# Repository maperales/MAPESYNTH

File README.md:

# MAPESYNTH
Documentación y ficheros de diseño y programación del sistema Mapesynth
-
En este repositorio se encuentra toda la información necesaria para poder replicar el sistema MAPESYNTH completo.

El sistema MAPESYNTH (Midi Advanced Programmable Educational Synthesizer) es un dispositivo que, convenientemente programado, puede hacer de instrumento MIDI, controlador MIDI, secuenciador MIDI y sintetizador MIDI, o cualquier combinación de las anteriores. Al ser de código abierto, puede ser reprogramado para cumplir otras funciones.

El hardware tiene la estructura de un Boosterpack tipo XL (40 pines), que se puede acomodar sobre multitud de Launchpads de Texas Instruments. En concreto, los ejemplos software y el diseño están enfocados al uso del microcontrolador MSP430FR5994, por lo que será necesario disponer del Launchpad MSP-EXP430FR5994 para su manejo. Los ficheros de diseño se encuentran en Eagle, aunque la etapa final se ha realizado en EasyEDA. Se ofrece igualmente el fichero de EasyEDA, por si sólo se desea fabricar tal cual, sin ningún cambio.

El software se ha desarrollado en Code Composer Studio, disponible de manera gratuita en la página de Texas Instruments. Probablemente se pueda reutilizar con algunos cambios menores con otros compiladores de la familia MSP430, aunque no se ha probado.

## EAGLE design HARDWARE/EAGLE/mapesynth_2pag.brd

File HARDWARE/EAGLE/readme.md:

Ficheros EAGLE
--
En principio, bastará con copiar los ficheros .brd y .sch en el mismo directorio para poder abrirlos. El fichero de librería (.lbr) se ofrece como compilación de los elementos, pero probablemente no sea necesario.

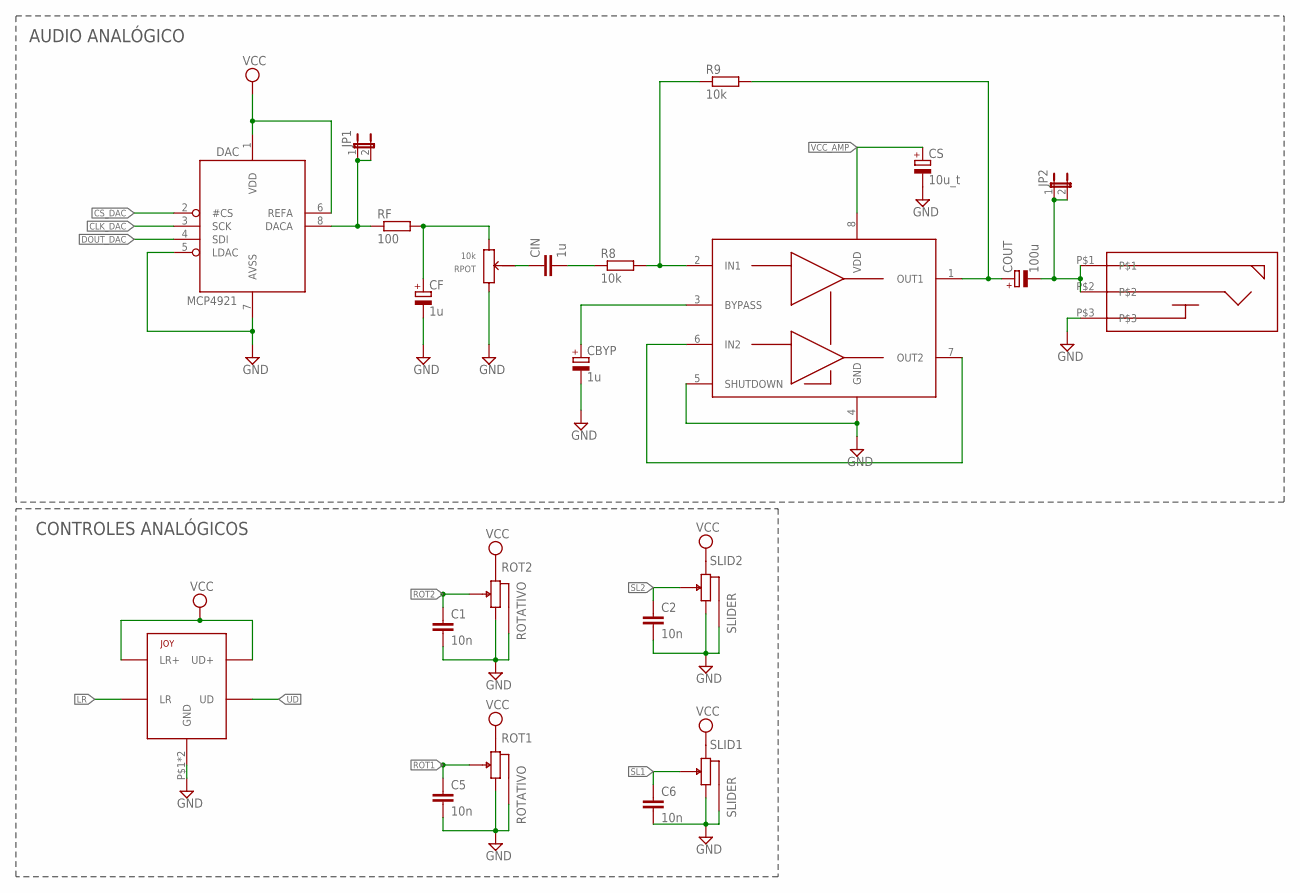
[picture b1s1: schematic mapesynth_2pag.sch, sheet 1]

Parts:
AMP: TPA6111; SO-08
C1, C2, C5, C6: 10n; C050-024X044
CBYP: 1u; 153CLV-0405
CF: 1u; 153CLV-0405
CIN: 1u; C1206
COUT: 100u; 153CLV-0605
CS: 10u_t; CT3528
DAC: MCP4921EN_SMD; SO-08
JOY: JOYSTICK; PLACAJSTICK
JP1, JP2: JP1E; JP1
R8, R9: 10k; M1206
RF: 100; M1206
ROT1, ROT2: ROTATIVO
RPOT: 10k; POT_VOL
SLID1, SLID2: SLIDER
U$4: JACK_3_5MM_VA; JACK3_5MM_V2

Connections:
CLK_DAC: DAC.3 (SCK); also elsewhere on the board
CS_DAC: DAC.2 (#CS); also elsewhere on the board
DOUT_DAC: DAC.4 (SDI); also elsewhere on the board
GND: AMP.4 (GND), AMP.5 (SHUTDOWN), C1.2, C2.2, C5.2, C6.2, CBYP.-, CF.-, CS.-, DAC.5 (LDAC), DAC.7 (AVSS), JOY.P$1 (GND), JOY.P$8 (GND), ROT1.A (1), ROT1.GND1 (GND), ROT1.GND2 (GND), ROT2.A (1), ROT2.GND1 (GND), ROT2.GND2 (GND), RPOT.P$1, SLID1.1, SLID1.4 (GND), SLID1.5 (GND), SLID1.6 (GND), SLID1.7 (GND), SLID2.1, SLID2.4 (GND), SLID2.5 (GND), SLID2.6 (GND), SLID2.7 (GND), U$4.P$3; also elsewhere on the board
LR: JOY.P$3 (LR), JOY.P$6 (LR); also elsewhere on the board
unnamed: DAC.8 (DACA), JP1.1, JP1.2, RF.1
unnamed: CF.+, RF.2, RPOT.P$3
unnamed: CIN.1, RPOT.P$2
unnamed: CIN.2, R8.1
unnamed: AMP.2 (IN1), R8.2, R9.1
unnamed: AMP.1 (OUT1), COUT.+, R9.2
unnamed: COUT.-, JP2.1, JP2.2, U$4.P$1, U$4.P$2
unnamed: AMP.6 (IN2), AMP.7 (OUT2)
unnamed: AMP.3 (BYPASS), CBYP.+
ROT1: C5.1, ROT1.C (2); also elsewhere on the board
ROT2: C1.1, ROT2.C (2); also elsewhere on the board
SL1: C6.1, SLID1.2; also elsewhere on the board
SL2: C2.1, SLID2.2; also elsewhere on the board
UD: JOY.P$2 (UD), JOY.P$7 (UD); also elsewhere on the board
VCC: DAC.1 (VDD), DAC.6 (REFA), JOY.P$4 (LR+), JOY.P$5 (UD+), ROT1.B (3), ROT2.B (3), SLID1.3, SLID2.3; also elsewhere on the board
VCC_AMP: AMP.8 (VDD), CS.+; also elsewhere on the board

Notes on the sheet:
AUDIO ANALÓGICO
CONTROLES ANALÓGICOS

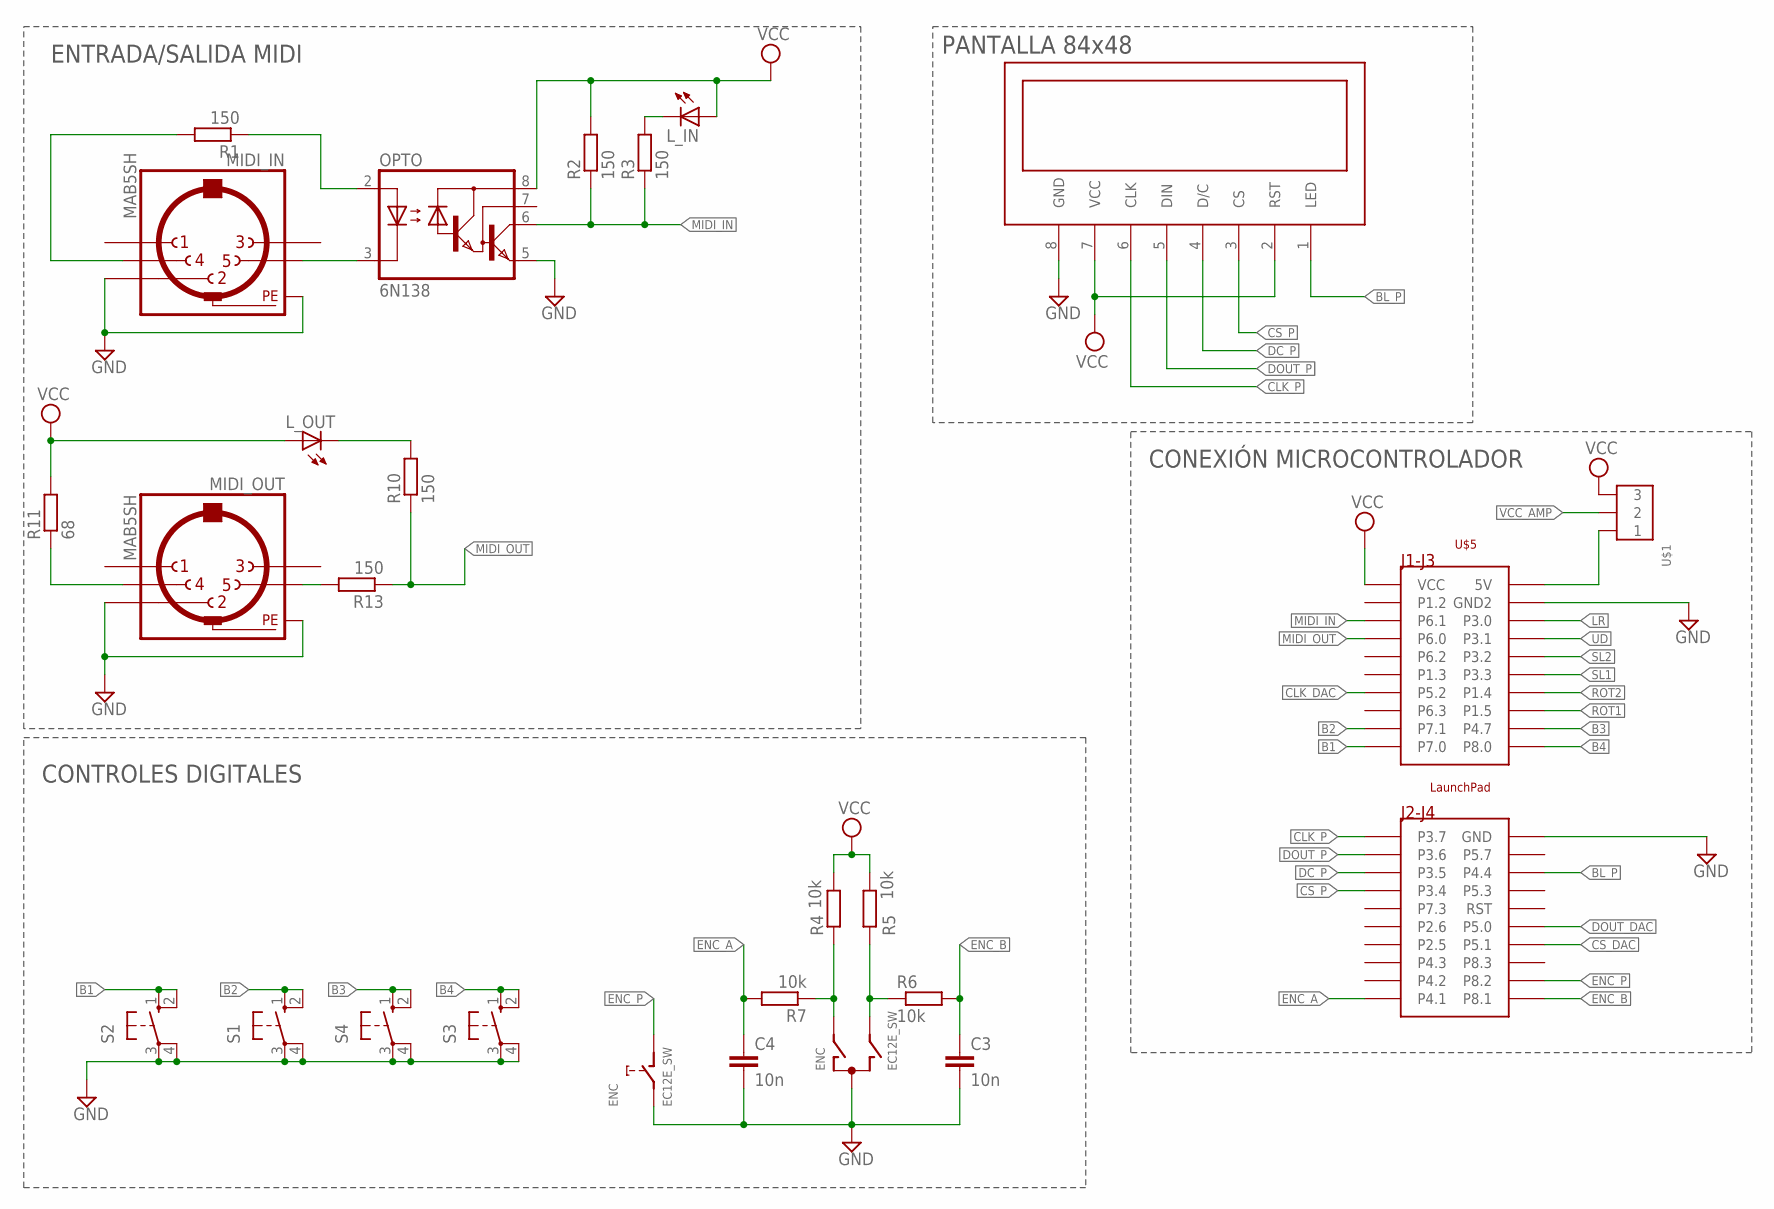
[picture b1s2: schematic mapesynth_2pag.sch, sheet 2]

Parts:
C3, C4: 10n; C050-024X044
ENC: EC12E_SW; ALPS_EC12E_SW
L_IN: LED5MM
L_OUT: LED5MM
MIDI_IN: MAB5SH
MIDI_OUT: MAB5SH
OPTO: 6N138; DIL08
R1, R2, R3, R10, R13: 150; 0207/10
R4, R5, R6, R7: 10k; R1206
R11: 68; 0207/10
S1, S2, S3, S4: 40-XX; B3F-40XX
U$1: JP3
U$3: NOKIA_5110
U$5: LAUNCHPAD_XL

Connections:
B1: S2.1 (S), S2.2 (S1), U$5.P$10 (P7.0)
B2: S1.1 (S), S1.2 (S1), U$5.P$9 (P7.1)
B3: S4.1 (S), S4.2 (S1), U$5.P$29 (P4.7)
B4: S3.1 (S), S3.2 (S1), U$5.P$30 (P8.0)
BL_P: U$3.1 (LED), U$5.P$18 (P4.4)
CLK_DAC: U$5.P$7 (P5.2); also elsewhere on the board
CLK_P: U$3.6 (CLK), U$5.P$40 (P3.7)
CS_DAC: U$5.P$14 (P5.1); also elsewhere on the board
CS_P: U$3.3 (CS), U$5.P$37 (P3.4)
DC_P: U$3.4 (D/C), U$5.P$38 (P3.5)
DOUT_DAC: U$5.P$15 (P5.0); also elsewhere on the board
DOUT_P: U$3.5 (DIN), U$5.P$39 (P3.6)
ENC_A: C4.1, R7.2, U$5.P$31 (P4.1)
ENC_B: C3.1, R6.2, U$5.P$11 (P8.1)
ENC_P: ENC.D (1), U$5.P$12 (P8.2)
GND: C3.2, C4.2, ENC.C, ENC.E (2), MIDI_IN.2, MIDI_IN.PE, MIDI_IN.PE@ (PE), MIDI_OUT.2, MIDI_OUT.PE, MIDI_OUT.PE@ (PE), OPTO.5 (GND), S1.3, S1.4 (P1), S2.3, S2.4 (P1), S3.3, S3.4 (P1), S4.3, S4.4 (P1), U$3.8 (GND), U$5.P$20 (GND), U$5.P$22 (GND2); also elsewhere on the board
LR: U$5.P$23 (P3.0); also elsewhere on the board
MIDI_IN: OPTO.6 (VO), R2.1, R3.1, U$5.P$3 (P6.1)
MIDI_OUT: R10.1, R13.1, U$5.P$4 (P6.0)
unnamed: MIDI_IN.4, R1.2
unnamed: MIDI_IN.5, OPTO.3 (C)
unnamed: OPTO.2 (A), R1.1
unnamed: U$1.P$1 (1), U$5.P$21 (5V)
unnamed: MIDI_OUT.4, R11.1
unnamed: L_IN.K (C), R3.2
unnamed: L_OUT.K (C), R10.2
unnamed: MIDI_OUT.5, R13.2
unnamed: ENC.A, R4.1, R7.1
unnamed: ENC.B, R5.1, R6.1
ROT1: U$5.P$28 (P1.5); also elsewhere on the board
ROT2: U$5.P$27 (P1.4); also elsewhere on the board
SL1: U$5.P$26 (P3.3); also elsewhere on the board
SL2: U$5.P$25 (P3.2); also elsewhere on the board
UD: U$5.P$24 (P3.1); also elsewhere on the board
VCC: L_IN.A, L_OUT.A, OPTO.8 (VCC), R2.2, R4.2, R5.2, R11.2, U$1.P$3 (3), U$3.2 (RST), U$3.7 (VCC), U$5.P$1 (VCC); also elsewhere on the board
VCC_AMP: U$1.P$2 (2); also elsewhere on the board

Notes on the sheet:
ENTRADA/SALIDA MIDI
PANTALLA 84x48
CONTROLES DIGITALES
CONEXIÓN MICROCONTROLADOR

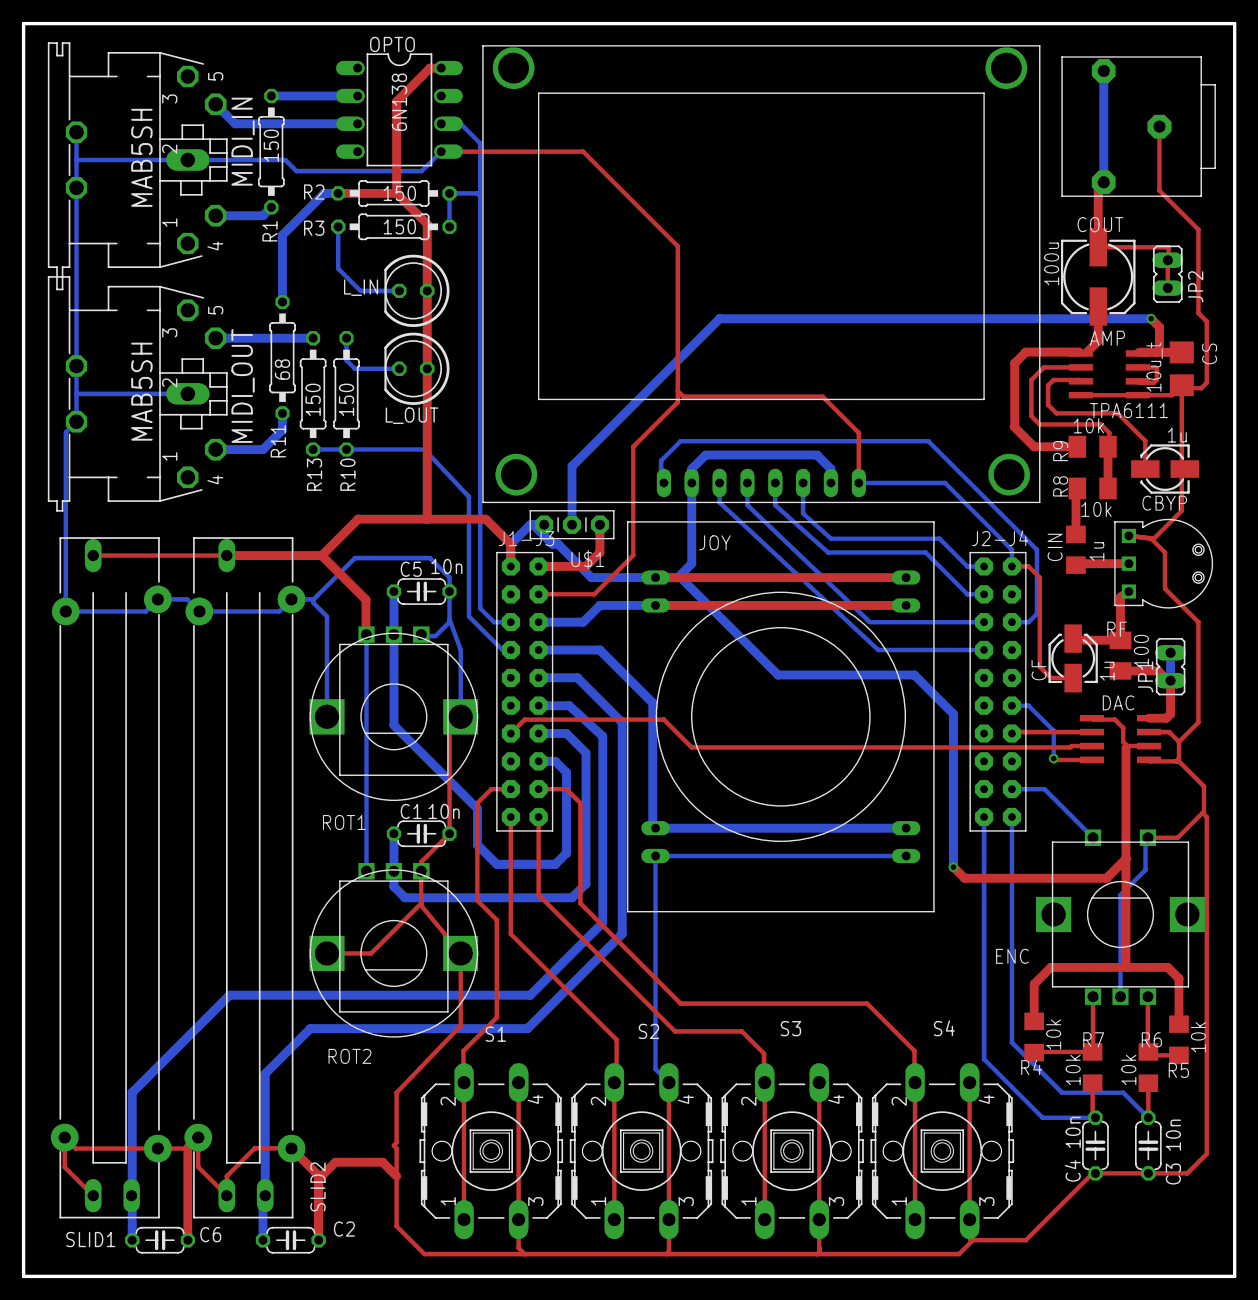
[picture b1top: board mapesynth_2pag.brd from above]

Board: 2 copper layers, 110.5 x 114.3 mm, 48 parts (0 on the bottom side), 45 nets.

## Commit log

2022-03-16 Add files via upload
    Fichero EasyEDA editable, con los retoques "cosméticos" en la capa de serigrafía.
2022-03-16 Fichero GERBER para fabricación
